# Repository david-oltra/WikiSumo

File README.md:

<H1>WikiSumo</H1>
<H2>Robot de competicion para la OSHWDEM 2024</H2>

<H2>Hardware</H2>

- ESP32-WROOM
- Sensores TOF VL53L0X
- Sensores IR QRE1113
- Motores N20 6V
- Regulador Voltaje LM2596S

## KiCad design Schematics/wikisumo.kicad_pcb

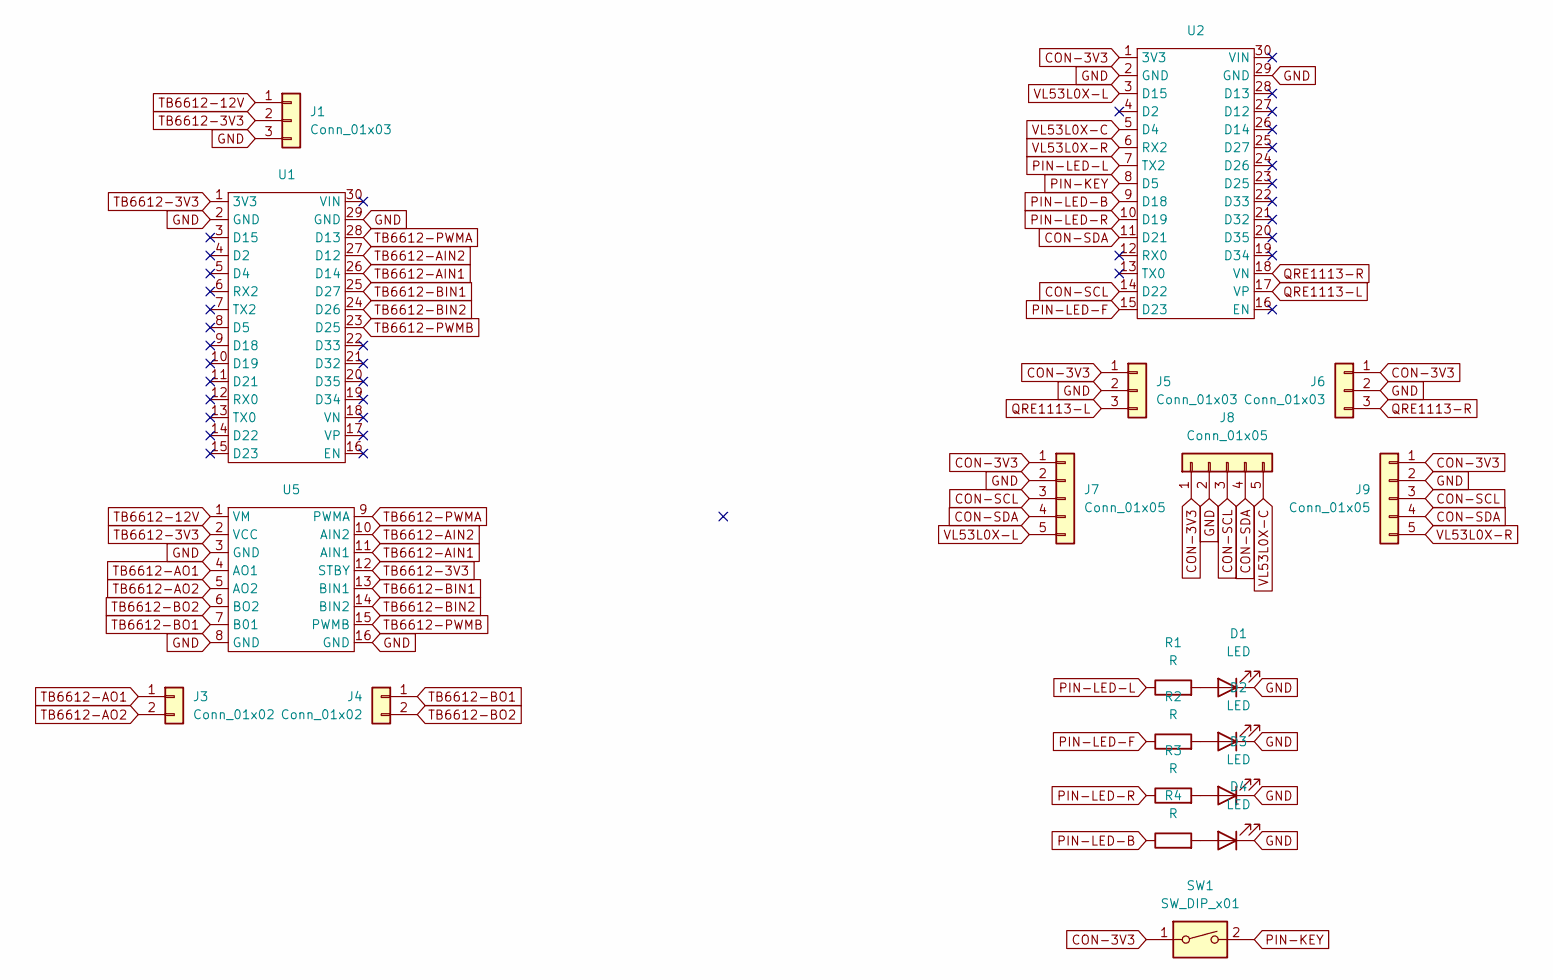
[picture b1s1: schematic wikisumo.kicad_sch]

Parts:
D1, D2, D3, D4: LED; LED_0805_2012Metric_Pad1.15x1.40mm_HandSolder
J1, J5, J6: Conn_01x03; JST_XH_B3B-XH-A_1x03_P2.50mm_Vertical
J3, J4: Conn_01x02; JST_XH_B2B-XH-A_1x02_P2.50mm_Vertical
J7, J8, J9: Conn_01x05; JST_XH_B5B-XH-A_1x05_P2.50mm_Vertical
R1, R2, R3, R4: R; R_0805_2012Metric_Pad1.20x1.40mm_HandSolder
SW1: SW_DIP_x01; SW_PUSH_6mm_H5mm
U1, U2: ESP32_DEVKITV1
U5: TB6612

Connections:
CON-3V3: J5.1, J6.1, J7.1, J8.1, J9.1, SW1.1, U2.1 (3V3)
CON-SCL: J7.3, J8.3, J9.3, U2.14 (D22)
CON-SDA: J7.4, J8.4, J9.4, U2.11 (D21)
GND: D1.1 (K), D2.1 (K), D3.1 (K), D4.1 (K), J1.3, J5.2, J6.2, J7.2, J8.2, J9.2, U1.2 (GND), U1.29 (GND), U2.2 (GND), U2.29 (GND), U5.3 (GND), U5.8 (GND), U5.16 (GND)
unnamed: D1.2 (A), R1.2
unnamed: D2.2 (A), R2.2
unnamed: D3.2 (A), R3.2
unnamed: D4.2 (A), R4.2
PIN-KEY: SW1.2, U2.8 (D5)
PIN-LED-B: R4.1, U2.9 (D18)
PIN-LED-F: R2.1, U2.15 (D23)
PIN-LED-L: R1.1, U2.7 (TX2)
PIN-LED-R: R3.1, U2.10 (D19)
QRE1113-L: J5.3, U2.17 (VP)
QRE1113-R: J6.3, U2.18 (VN)
TB6612-3V3: J1.2, U1.1 (3V3), U5.2 (VCC), U5.12 (STBY)
TB6612-12V: J1.1, U5.1 (VM)
TB6612-AIN1: U1.26 (D14), U5.11 (AIN1)
TB6612-AIN2: U1.27 (D12), U5.10 (AIN2)
TB6612-AO1: J3.1, U5.4 (AO1)
TB6612-AO2: J3.2, U5.5 (AO2)
TB6612-BIN1: U1.25 (D27), U5.13 (BIN1)
TB6612-BIN2: U1.24 (D26), U5.14 (BIN2)
TB6612-BO1: J4.1, U5.7 (B01)
TB6612-BO2: J4.2, U5.6 (BO2)
TB6612-PWMA: U1.28 (D13), U5.9 (PWMA)
TB6612-PWMB: U1.23 (D25), U5.15 (PWMB)
VL53L0X-C: J8.5, U2.5 (D4)
VL53L0X-L: J7.5, U2.3 (D15)
VL53L0X-R: J9.5, U2.6 (RX2)

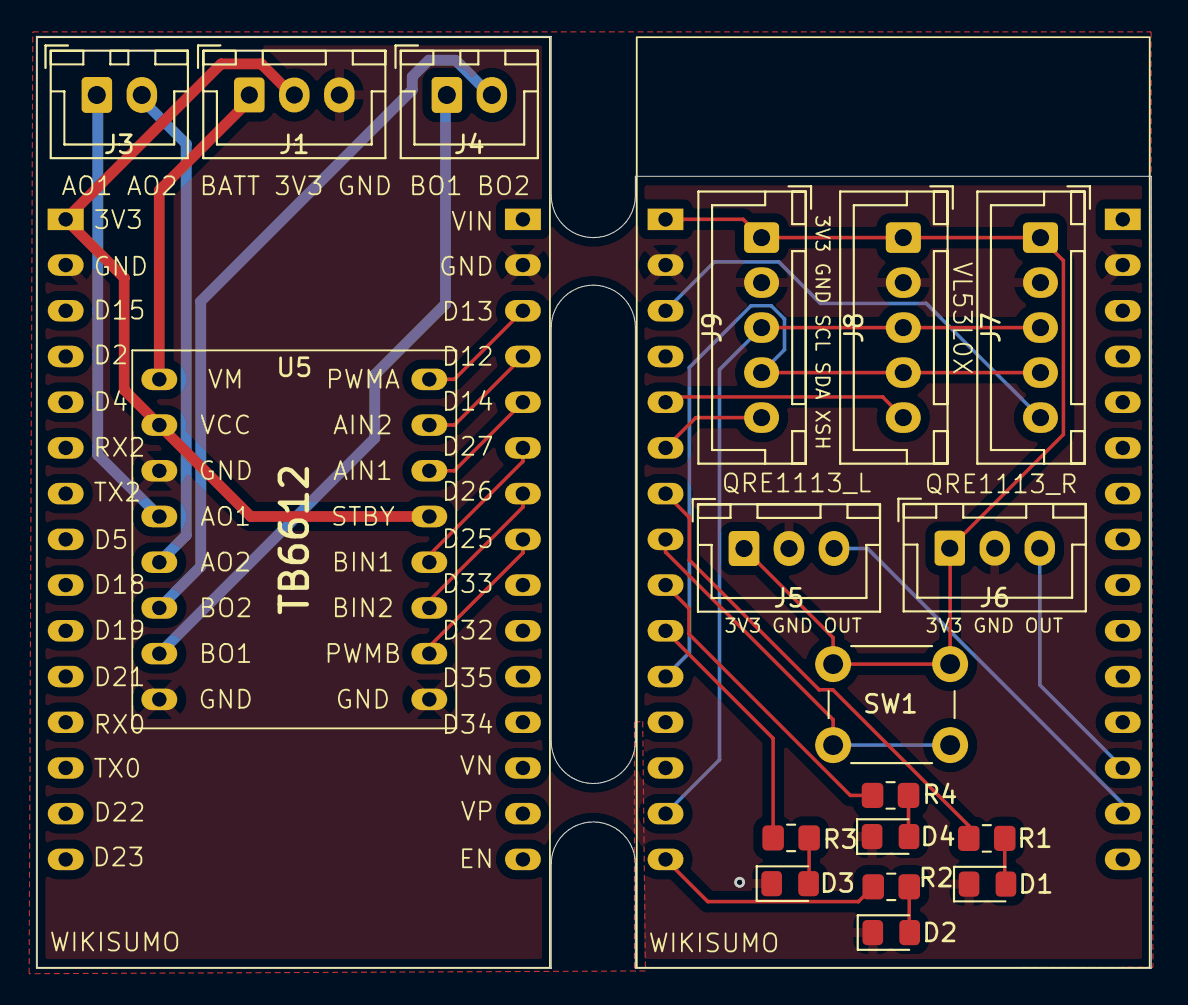
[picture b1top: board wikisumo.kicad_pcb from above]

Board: 2 copper layers, 61.9 x 51.8 mm, 20 parts (0 on the bottom side), 30 nets.

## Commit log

2023-11-09 Rewrite code
2023-11-15 Rewrite code, add rotary enconder library
2023-11-15 rm libs
2023-11-16 add VL53L0X
2023-11-17 QRE1113 Lib Update
2023-11-18 Debug TB6612
2024-03-30 change rotary to switch
2024-03-30 restore
2024-04-06 Add OTA
2024-10-04 add STL
2024-10-05 write code
